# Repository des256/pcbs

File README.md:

# PCBs

Making electronics as well

## Prerequisites

KiCad 10.0
install plugin: impart GUI for KiCad
install plugin: Fabrication Toolkit
install plugin: wDark Theme
install repository: CD_FER's KiCad repository (https://raw.githubusercontent.com/CDFER/cd_fer-kicad-repository/main/repository.json)
install plugin: JLCPCB: KiCad Library

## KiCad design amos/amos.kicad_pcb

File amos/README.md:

# Amos

Jetson helper board (USB3 + 12V RS-485 Servo + 5V UART Servo)

Input Power: 19V laptop
Output Power: 19V jetson + 12V (10A..20A) servo + 5V (5A..10A) servo + 5V (5A) USB

Upstream USB Hub: USB3-C
Downstream USB Hub: 3x USB3-A + 1x internal to CH344Q

each servo bus either 12V 4-pin RS-485 or 5V 3-pin UART
selectable with DIP

## Schematic Sheets

2: Main Power + Jetson
3: Buck 12V 10A..20A
4: Buck 5V 5A..10A
5: Buck 5V USB
6: Buck 3V3 + 1V1
7: USB HUB
8: CH344Q
9: Servo A
10: Servo B
11: Servo C
12: Servo D
13: USB A
14: USB B
15: USB C

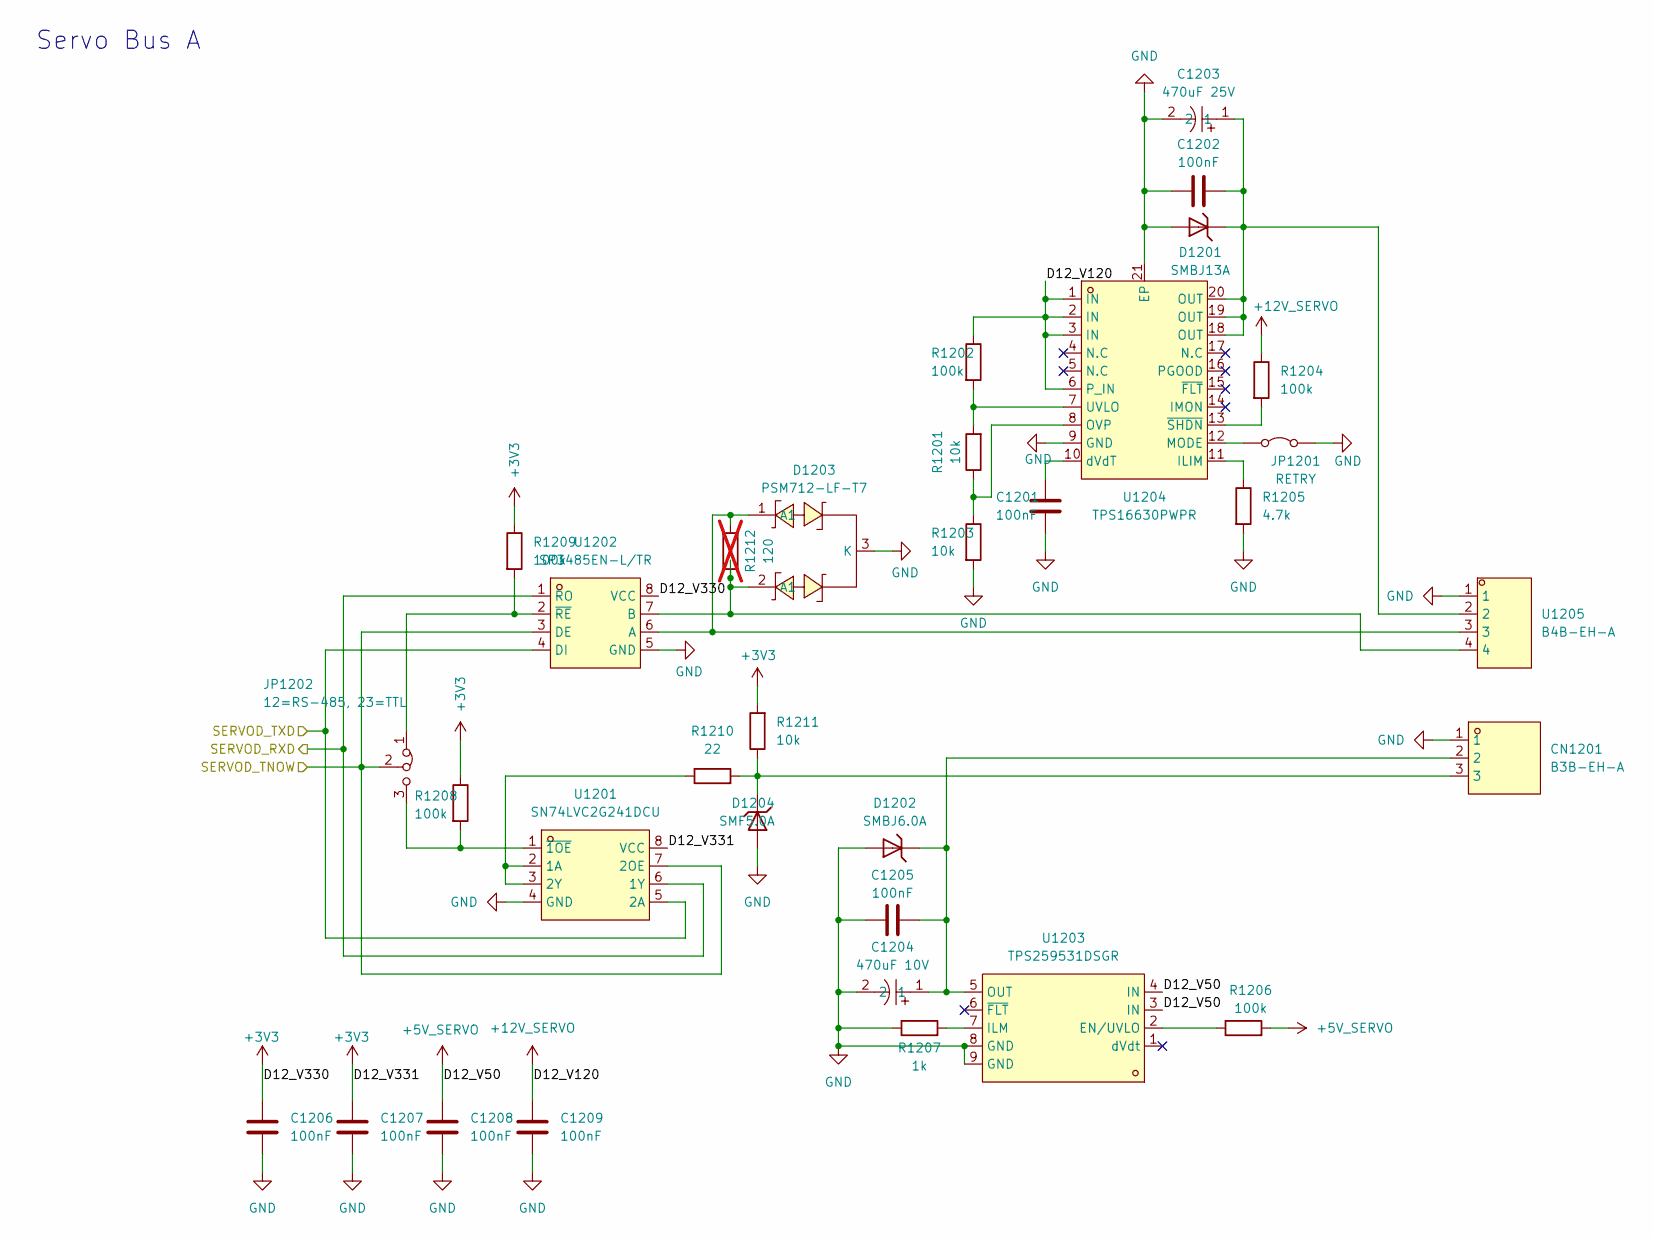
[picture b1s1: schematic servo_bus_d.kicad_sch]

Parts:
C1201, C1202, C1205: 100nF; C_0402_1005Metric; LCSC C307331
C1203: 470uF 25V; CP_Elec_8x10.5; LCSC C46550466
C1204: 470uF 10V; CP_Elec_6.3x7.7; LCSC C46550459
C1206, C1207, C1208, C1209: 100nF; C_0402_1005Metric; LCSC Part C14663
CN1201: B3B-EH-A; CONN-TH_B3B-EH-A-LF-SN; MPN B3B-EH-A(LF)(SN); LCSC Part C160259
D1201: SMBJ13A; SMB_L4.4-W3.6-LS5.3-RD; LCSC C19077567
D1202: SMBJ6.0A; SMB_L4.4-W3.6-LS5.3-RD; LCSC C19077560
D1203: PSM712-LF-T7; SOT-23-3_L3.0-W1.7-P0.95-LS2.9-BR; MPN PSM712-LF-T7; LCSC Part C32677
D1204: SMF5.0A; SOD-123FL_L2.8-W1.9-LS3.7-RD; LCSC C19077497
JP1201: RETRY; PinHeader_1x02_P2.54mm_Vertical; MPN PZ254V-11-02P; LCSC Part C492401
JP1202: 12=RS-485, 23=TTL; PinHeader_1x03_P2.54mm_Vertical; MPN PZ254V-11-03P; LCSC Part C2937625
R1201, R1203, R1211: 10k; R_0402_1005Metric; LCSC C25744
R1202, R1204, R1206, R1208, R1209: 100k; R_0402_1005Metric; LCSC C25741
R1205: 4.7k; R_0402_1005Metric; LCSC C25900
R1207: 1k; R_0402_1005Metric; LCSC C11702
R1210: 22; R_0402_1005Metric; LCSC C25092
R1212: 120; R_0603; LCSC C22787; not fitted
U1201: SN74LVC2G241DCU; VSSOP-8_L2.3-W2.0-P0.50-LS3.1-BR; MPN SN74LVC2G241DCUR; LCSC Part C10430
U1202: SP3485EN-L/TR; SOIC-8_L5.0-W4.0-P1.27-LS6.0-BL; MPN SP3485EN-L/TR; LCSC Part C8963
U1203: TPS259531DSGR; WSON-8_L2.0-W2.0-P0.50-TL-EP; MPN TPS259531DSGR; LCSC Part C2155674
U1204: TPS16630PWPR; HTSSOP-20_L6.5-W4.4-P0.65-LS6.4-TL-EP2.58; MPN TPS16630PWPR; LCSC Part C1849461
U1205: B4B-EH-A; CONN-TH_B4B-EH-A-LF-SN; MPN B4B-EH-A(LF)(SN); LCSC Part C160258

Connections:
+3V3: C1206.1, C1207.1, R1208.1, R1209.1, R1211.2, U1201.8 (VCC), U1202.8 (VCC); also elsewhere on the board
+5V_SERVO: C1208.1, R1206.2, U1203.3 (IN), U1203.4 (IN); also elsewhere on the board
+12V_SERVO: C1209.1, R1202.1, R1204.1, U1204.1 (IN), U1204.2 (IN), U1204.3 (IN), U1204.6 (P_IN); also elsewhere on the board
/SERVOD_RXD: U1201.6 (1Y), U1202.1 (RO); also elsewhere on the board
/SERVOD_TNOW: JP1202.2 (C), U1201.7 (2OE), U1202.3 (DE); also elsewhere on the board
/SERVOD_TXD: U1201.5 (2A), U1202.4 (DI); also elsewhere on the board
GND: C1201.2, C1202.1, C1203.2, C1204.2, C1205.1, C1206.2, C1207.2, C1208.2, C1209.2, CN1201.1, D1201.2, D1202.2, D1203.3 (K), D1204.2, JP1201.2 (B), R1203.2, R1205.2, R1207.1, U1201.4 (GND), U1202.5 (GND), U1203.8 (GND), U1203.9 (GND), U1204.9 (GND), U1204.21 (EP), U1205.1; also elsewhere on the board
unnamed: C1202.2, C1203.1, D1201.1, U1204.18 (OUT), U1204.19 (OUT), U1204.20 (OUT), U1205.2
unnamed: CN1201.3, D1204.1, R1210.2, R1211.1
unnamed: JP1201.1 (A), U1204.12 (MODE)
unnamed: JP1202.1 (A), R1209.2, U1202.2 (~RE)
unnamed: JP1202.3 (B), R1208.2, U1201.1 (~1OE)
unnamed: R1210.1, U1201.2 (1A), U1201.3 (2Y)
unnamed: D1203.1 (A1), R1212.1, U1202.6 (A), U1205.3
unnamed: D1203.2 (A1), R1212.2, U1202.7 (B), U1205.4
unnamed: R1206.1, U1203.2 (EN/UVLO)
unnamed: R1207.2, U1203.7 (ILM)
unnamed: C1204.1, C1205.2, CN1201.2, D1202.1, U1203.5 (OUT)
unnamed: R1205.1, U1204.11 (ILIM)
unnamed: R1201.1, R1203.1, U1204.8 (OVP)
unnamed: R1201.2, R1202.2, U1204.7 (UVLO)
unnamed: C1201.1, U1204.10 (dVdT)
unnamed: R1204.2, U1204.13 (~SHDN)

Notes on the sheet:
Servo Bus A

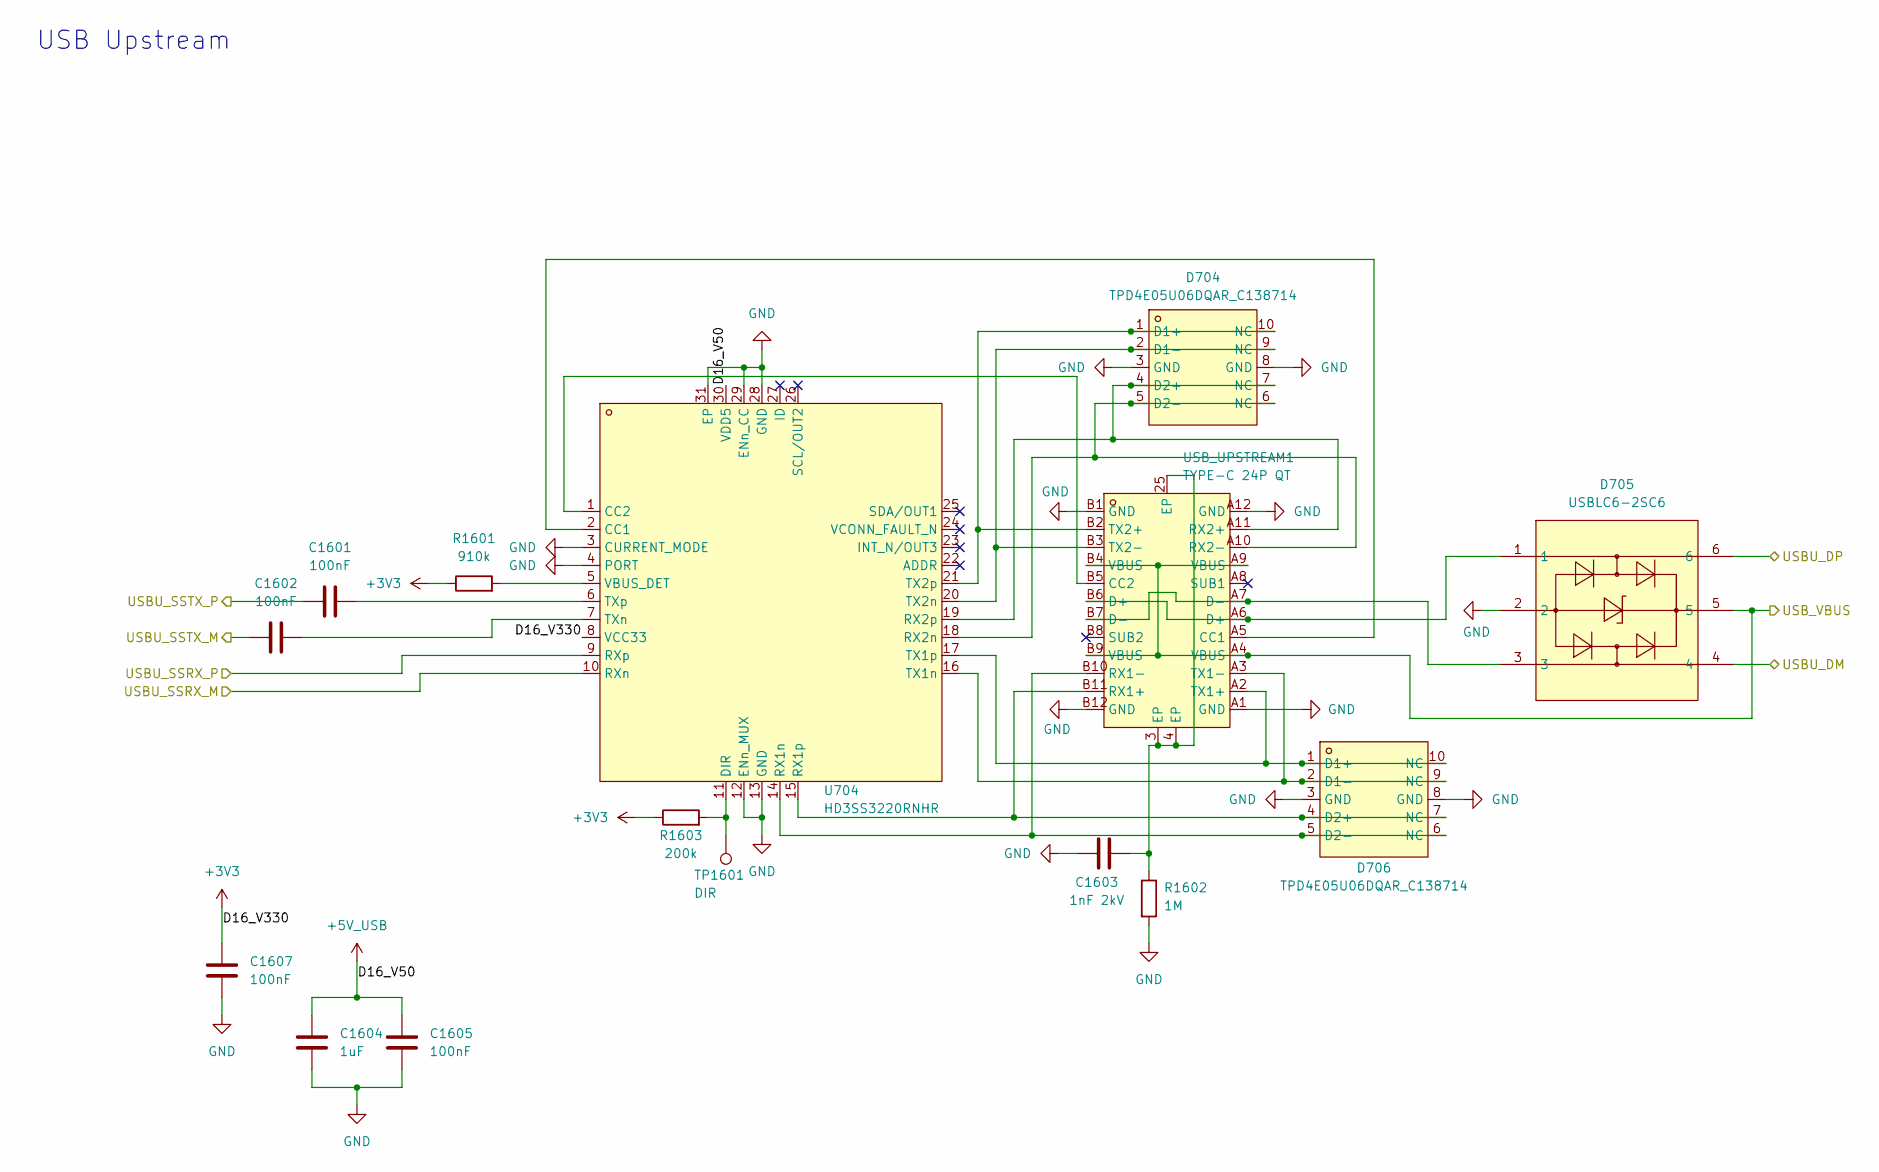
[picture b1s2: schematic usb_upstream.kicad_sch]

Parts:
C1601, C1602: 100nF; C_0402_1005Metric; LCSC C307331
C1603: 1nF 2kV; C_1206_3216Metric; LCSC C9196
C1604: 1uF; C_0402_1005Metric; LCSC Part C15849
C1605, C1607: 100nF; C_0402_1005Metric; LCSC Part C14663
D704, D706: TPD4E05U06DQAR_C138714; USON-10_L2.5-W1.0-P0.50-BL; MPN TPD4E05U06DQAR; LCSC Part C138714
D705: USBLC6-2SC6; SOT-23-6_L2.9-W1.6-P0.95-LS2.8-BL; MPN USBLC6-2SC6; LCSC Part C7519
R1601: 910k; R_0402_1005Metric; LCSC C25800
R1602: 1M; R_0402_1005Metric; LCSC C26083
R1603: 200k; R_0402_1005Metric; LCSC C25764
TP1601: DIR; TestPoint_Pad_1.0x1.0mm
U704: HD3SS3220RNHR; WQFN-30_L4.5-W2.5-P0.4-BL-EP; MPN HD3SS3220RNHR; LCSC Part C165155
USB_UPSTREAM1: TYPE-C 24P QT; USB-C-SMD_TYPE-C-24P-QT; MPN TYPE-C 24P QT; LCSC Part C2681555

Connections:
+3V3: C1607.1, R1601.1, R1603.1, U704.8 (VCC33); also elsewhere on the board
+5V_USB: C1604.1, C1605.1, U704.30 (VDD5); also elsewhere on the board
/USBU_DM: D705.4; also elsewhere on the board
/USBU_DP: D705.6; also elsewhere on the board
/USBU_SSRX_M: U704.10 (RXn); also elsewhere on the board
/USBU_SSRX_P: U704.9 (RXp); also elsewhere on the board
/USBU_SSTX_M: C1602.1; also elsewhere on the board
/USBU_SSTX_P: C1601.1; also elsewhere on the board
/USB_VBUS: D705.5, USB_UPSTREAM1.A4 (VBUS), USB_UPSTREAM1.A9 (VBUS), USB_UPSTREAM1.B4 (VBUS), USB_UPSTREAM1.B9 (VBUS); also elsewhere on the board
GND: C1603.1, C1604.2, C1605.2, C1607.2, D704.3 (GND), D704.8 (GND), D705.2, D706.3 (GND), D706.8 (GND), R1602.2, U704.3 (CURRENT_MODE), U704.4 (PORT), U704.12 (ENn_MUX), U704.13 (GND), U704.28 (GND), U704.29 (ENn_CC), U704.31 (EP), USB_UPSTREAM1.A1 (GND), USB_UPSTREAM1.A12 (GND), USB_UPSTREAM1.B1 (GND), USB_UPSTREAM1.B12 (GND); also elsewhere on the board
unnamed: C1603.2, R1602.1, USB_UPSTREAM1.3 (EP), USB_UPSTREAM1.4 (EP), USB_UPSTREAM1.25 (EP)
unnamed: D704.1 (D1+), D704.10 (NC), U704.21 (TX2p), USB_UPSTREAM1.B2 (TX2+)
unnamed: D704.2 (D1-), D704.9 (NC), U704.20 (TX2n), USB_UPSTREAM1.B3 (TX2-)
unnamed: D704.4 (D2+), D704.7 (NC), U704.19 (RX2p), USB_UPSTREAM1.A11 (RX2+)
unnamed: D704.5 (D2-), D704.6 (NC), U704.18 (RX2n), USB_UPSTREAM1.A10 (RX2-)
unnamed: D705.1, USB_UPSTREAM1.A6 (D+), USB_UPSTREAM1.B6 (D+)
unnamed: D705.3, USB_UPSTREAM1.A7 (D-), USB_UPSTREAM1.B7 (D-)
unnamed: D706.1 (D1+), D706.10 (NC), U704.17 (TX1p), USB_UPSTREAM1.A2 (TX1+)
unnamed: D706.2 (D1-), D706.9 (NC), U704.16 (TX1n), USB_UPSTREAM1.A3 (TX1-)
unnamed: D706.4 (D2+), D706.7 (NC), U704.15 (RX1p), USB_UPSTREAM1.B11 (RX1+)
unnamed: D706.5 (D2-), D706.6 (NC), U704.14 (RX1n), USB_UPSTREAM1.B10 (RX1-)
unnamed: U704.2 (CC1), USB_UPSTREAM1.A5 (CC1)
unnamed: U704.1 (CC2), USB_UPSTREAM1.B5 (CC2)
unnamed: R1603.2, TP1601.1 (1_1), U704.11 (DIR)
unnamed: C1602.2, U704.7 (TXn)
unnamed: C1601.2, U704.6 (TXp)
unnamed: R1601.2, U704.5 (VBUS_DET)

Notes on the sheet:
USB Upstream

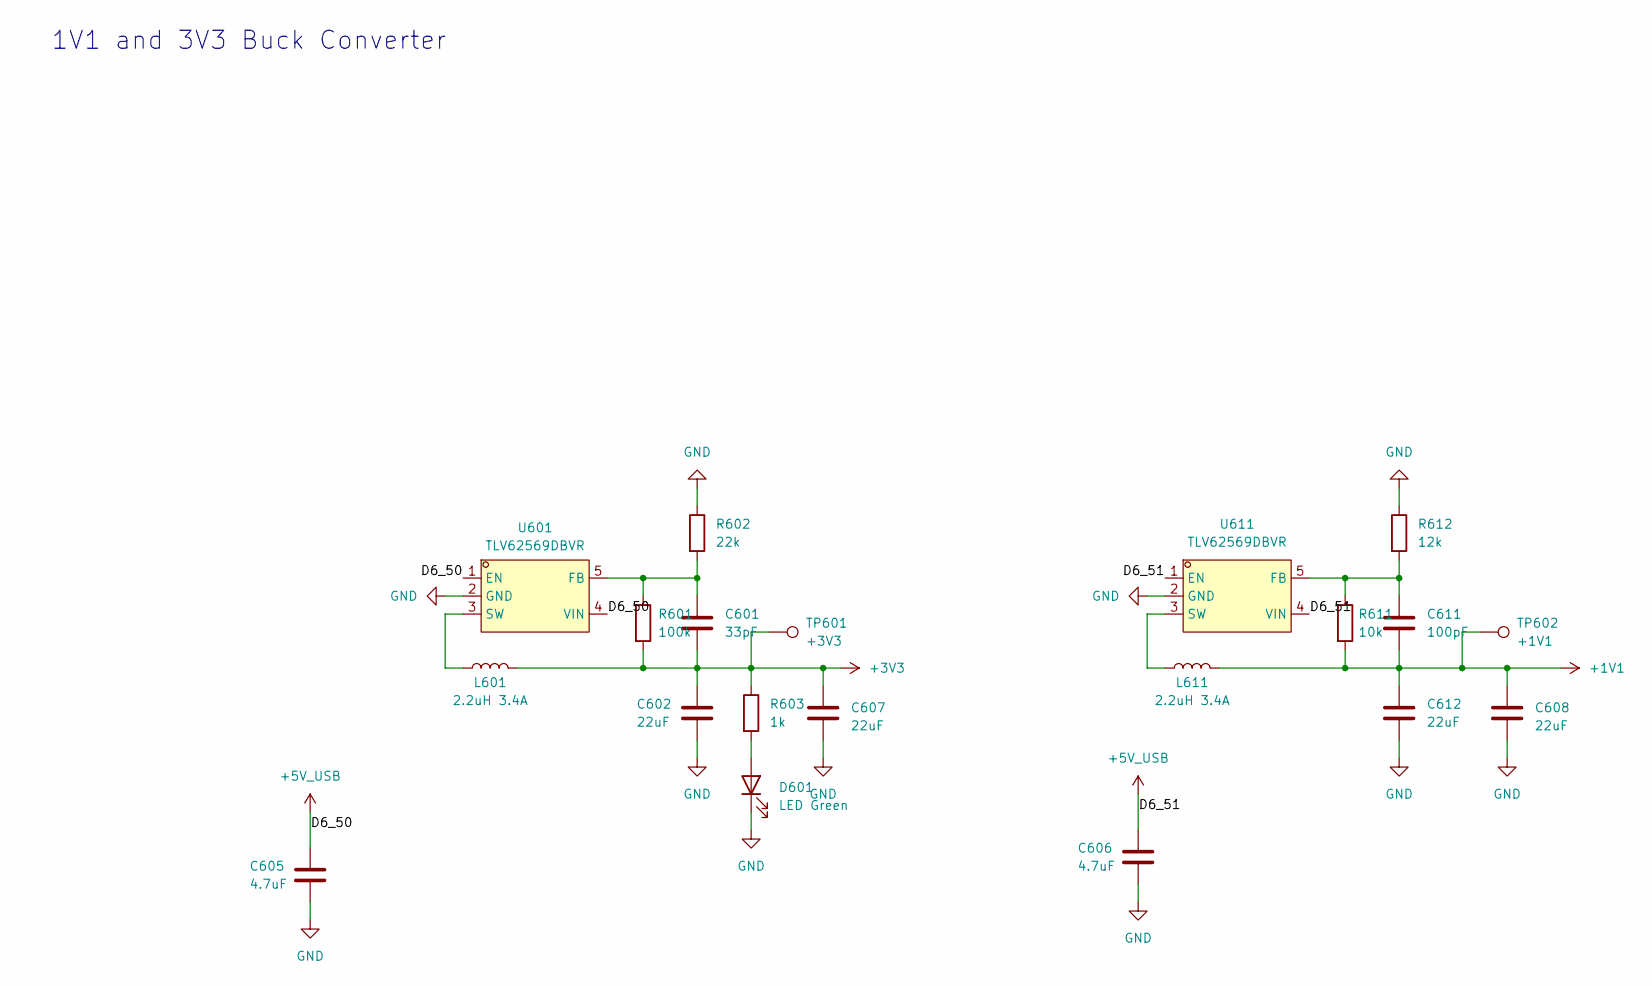
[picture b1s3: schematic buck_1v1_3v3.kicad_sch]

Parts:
C601: 33pF; C_0402_1005Metric; LCSC Part C1562
C602, C607, C608, C612: 22uF; C_0805_2012Metric; LCSC Part C45783
C605, C606: 4.7uF; C_0805_2012Metric; LCSC Part C1779
C611: 100pF; C_0402_1005Metric; LCSC Part C1546
D601: LED Green; LED_0805_2012Metric; LCSC C2297
L601, L611: 2.2uH 3.4A; IND-SMD_L4.0-W4.0_LQH44PN2R2MP0L; MPN SMNR4020-2.2UH; LCSC Part C135262
R601: 100k; R_0402_1005Metric; LCSC C25741
R602: 22k; R_0402_1005Metric; LCSC C25768
R603: 1k; R_0402_1005Metric; LCSC C11702
R611: 10k; R_0402_1005Metric; LCSC C25744
R612: 12k; R_0402_1005Metric; LCSC C25752
TP601: +3V3; TestPoint_Pad_1.0x1.0mm
TP602: +1V1; TestPoint_Pad_1.0x1.0mm
U601, U611: TLV62569DBVR; SOT-23-5_L3.0-W1.7-P0.95-LS2.8-BR; MPN TLV62569DBVR; LCSC Part C141836

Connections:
+1V1: C608.1, C611.2, C612.1, L611.2, R611.2, TP602.1 (1_1); also elsewhere on the board
+3V3: C601.2, C602.1, C607.1, L601.2, R601.2, R603.1, TP601.1 (1_1); also elsewhere on the board
+5V_USB: C605.1, C606.1, U601.1 (EN), U601.4 (VIN), U611.1 (EN), U611.4 (VIN); also elsewhere on the board
GND: C602.2, C605.2, C606.2, C607.2, C608.2, C612.2, D601.1 (K), R602.1, R612.1, U601.2 (GND), U611.2 (GND); also elsewhere on the board
unnamed: D601.2 (A), R603.2
unnamed: C601.1, R601.1, R602.2, U601.5 (FB)
unnamed: L601.1, U601.3 (SW)
unnamed: C611.1, R611.1, R612.2, U611.5 (FB)
unnamed: L611.1, U611.3 (SW)

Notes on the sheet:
1V1 and 3V3 Buck Converter

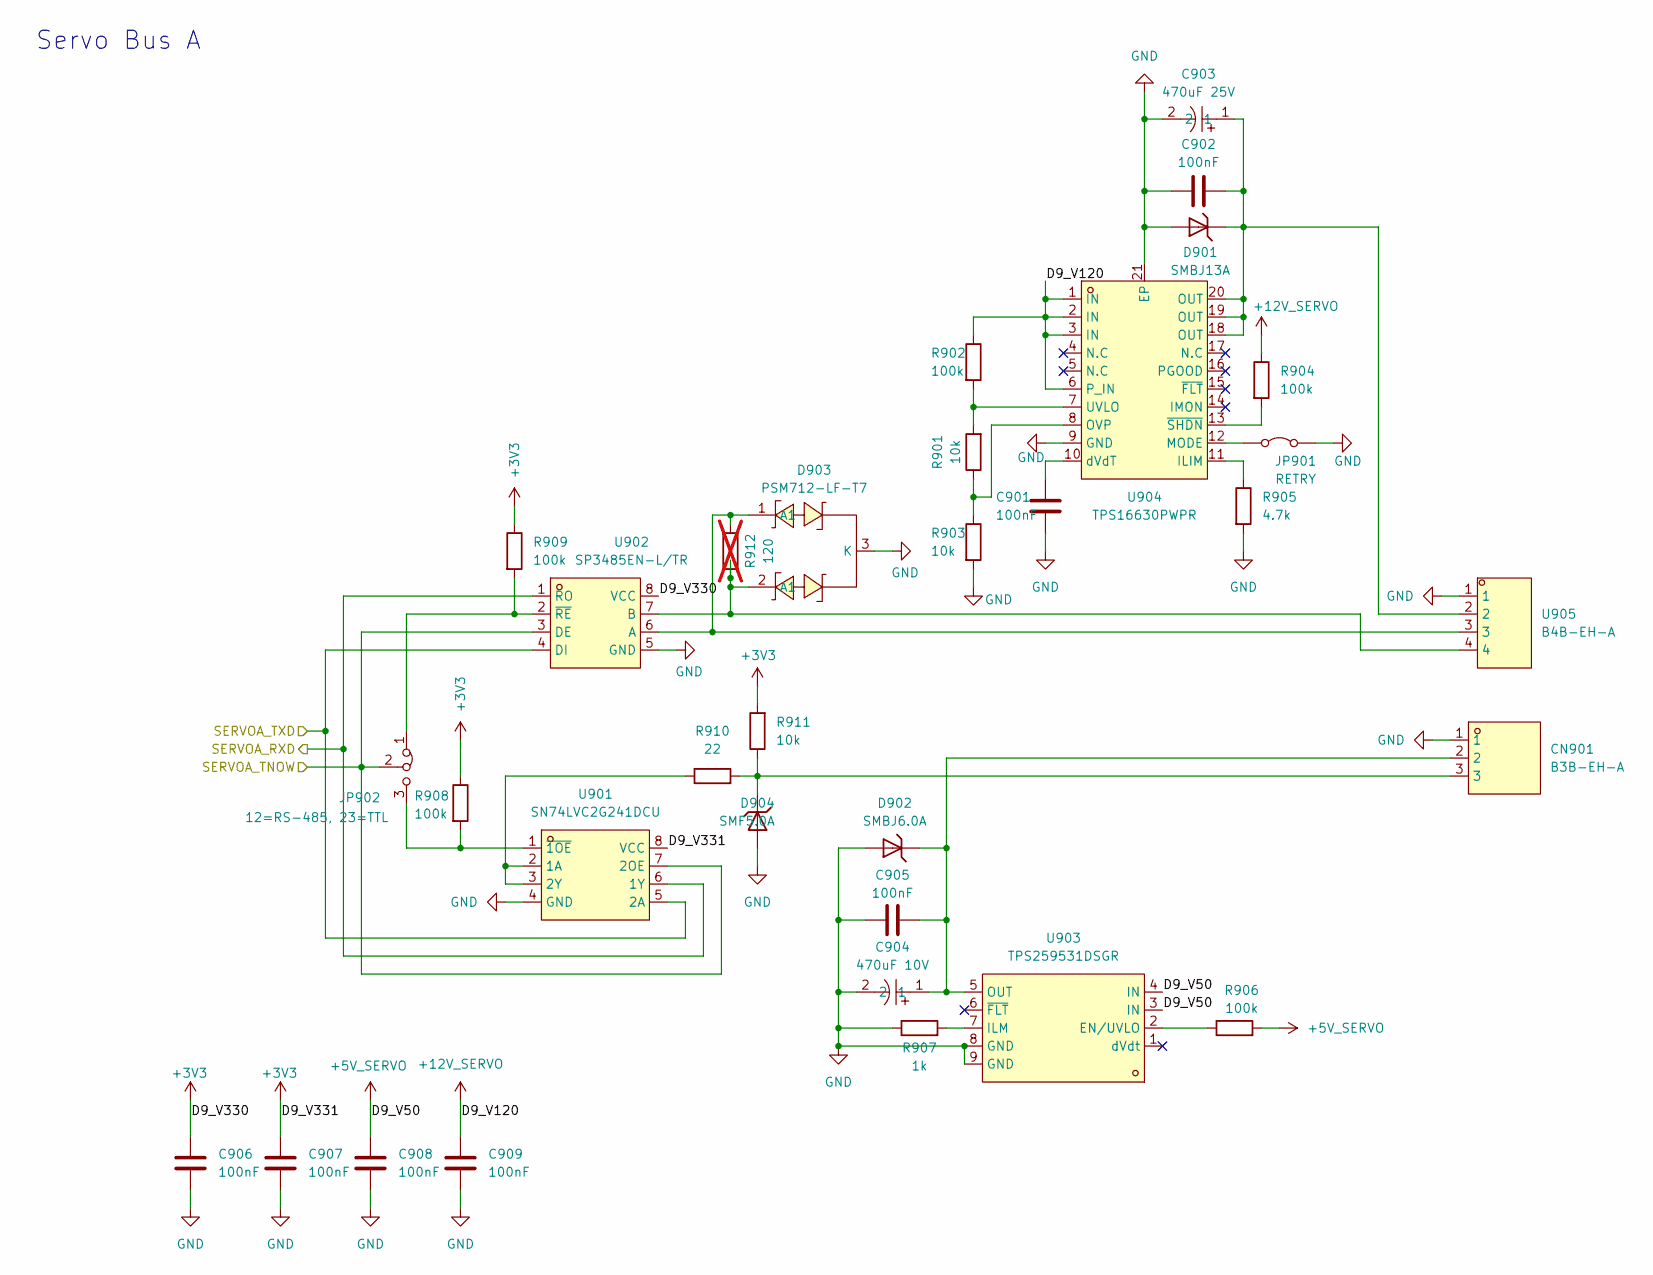
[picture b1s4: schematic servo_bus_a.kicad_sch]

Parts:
C901, C902, C905: 100nF; C_0402_1005Metric; LCSC C307331
C903: 470uF 25V; CP_Elec_8x10.5; LCSC C46550466
C904: 470uF 10V; CP_Elec_6.3x7.7; LCSC C46550459
C906, C907, C908, C909: 100nF; C_0402_1005Metric; LCSC Part C14663
CN901: B3B-EH-A; CONN-TH_B3B-EH-A-LF-SN; MPN B3B-EH-A(LF)(SN); LCSC Part C160259
D901: SMBJ13A; SMB_L4.4-W3.6-LS5.3-RD; LCSC C19077567
D902: SMBJ6.0A; SMB_L4.4-W3.6-LS5.3-RD; LCSC C19077560
D903: PSM712-LF-T7; SOT-23-3_L3.0-W1.7-P0.95-LS2.9-BR; MPN PSM712-LF-T7; LCSC Part C32677
D904: SMF5.0A; SOD-123FL_L2.8-W1.9-LS3.7-RD; LCSC C19077497
JP901: RETRY; PinHeader_1x02_P2.54mm_Vertical; MPN PZ254V-11-02P; LCSC Part C492401
JP902: 12=RS-485, 23=TTL; PinHeader_1x03_P2.54mm_Vertical; MPN PZ254V-11-03P; LCSC Part C2937625
R901, R903, R911: 10k; R_0402_1005Metric; LCSC C25744
R902, R904, R906, R908, R909: 100k; R_0402_1005Metric; LCSC C25741
R905: 4.7k; R_0402_1005Metric; LCSC C25900
R907: 1k; R_0402_1005Metric; LCSC C11702
R910: 22; R_0402_1005Metric; LCSC C25092
R912: 120; R_0603; LCSC C22787; not fitted
U901: SN74LVC2G241DCU; VSSOP-8_L2.3-W2.0-P0.50-LS3.1-BR; MPN SN74LVC2G241DCUR; LCSC Part C10430
U902: SP3485EN-L/TR; SOIC-8_L5.0-W4.0-P1.27-LS6.0-BL; MPN SP3485EN-L/TR; LCSC Part C8963
U903: TPS259531DSGR; WSON-8_L2.0-W2.0-P0.50-TL-EP; MPN TPS259531DSGR; LCSC Part C2155674
U904: TPS16630PWPR; HTSSOP-20_L6.5-W4.4-P0.65-LS6.4-TL-EP2.58; MPN TPS16630PWPR; LCSC Part C1849461
U905: B4B-EH-A; CONN-TH_B4B-EH-A-LF-SN; MPN B4B-EH-A(LF)(SN); LCSC Part C160258

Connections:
+3V3: C906.1, C907.1, R908.1, R909.1, R911.2, U901.8 (VCC), U902.8 (VCC); also elsewhere on the board
+5V_SERVO: C908.1, R906.2, U903.3 (IN), U903.4 (IN); also elsewhere on the board
+12V_SERVO: C909.1, R902.1, R904.1, U904.1 (IN), U904.2 (IN), U904.3 (IN), U904.6 (P_IN); also elsewhere on the board
/SERVOA_RXD: U901.6 (1Y), U902.1 (RO); also elsewhere on the board
/SERVOA_TNOW: JP902.2 (C), U901.7 (2OE), U902.3 (DE); also elsewhere on the board
/SERVOA_TXD: U901.5 (2A), U902.4 (DI); also elsewhere on the board
GND: C901.2, C902.1, C903.2, C904.2, C905.1, C906.2, C907.2, C908.2, C909.2, CN901.1, D901.2, D902.2, D903.3 (K), D904.2, JP901.2 (B), R903.2, R905.2, R907.1, U901.4 (GND), U902.5 (GND), U903.8 (GND), U903.9 (GND), U904.9 (GND), U904.21 (EP), U905.1; also elsewhere on the board
unnamed: C902.2, C903.1, D901.1, U904.18 (OUT), U904.19 (OUT), U904.20 (OUT), U905.2
unnamed: CN901.3, D904.1, R910.2, R911.1
unnamed: JP901.1 (A), U904.12 (MODE)
unnamed: JP902.1 (A), R909.2, U902.2 (~RE)
unnamed: JP902.3 (B), R908.2, U901.1 (~1OE)
unnamed: R910.1, U901.2 (1A), U901.3 (2Y)
unnamed: D903.1 (A1), R912.1, U902.6 (A), U905.3
unnamed: D903.2 (A1), R912.2, U902.7 (B), U905.4
unnamed: R906.1, U903.2 (EN/UVLO)
unnamed: R907.2, U903.7 (ILM)
unnamed: C904.1, C905.2, CN901.2, D902.1, U903.5 (OUT)
unnamed: R905.1, U904.11 (ILIM)
unnamed: R901.1, R903.1, U904.8 (OVP)
unnamed: R901.2, R902.2, U904.7 (UVLO)
unnamed: C901.1, U904.10 (dVdT)
unnamed: R904.2, U904.13 (~SHDN)

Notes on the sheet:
Servo Bus A

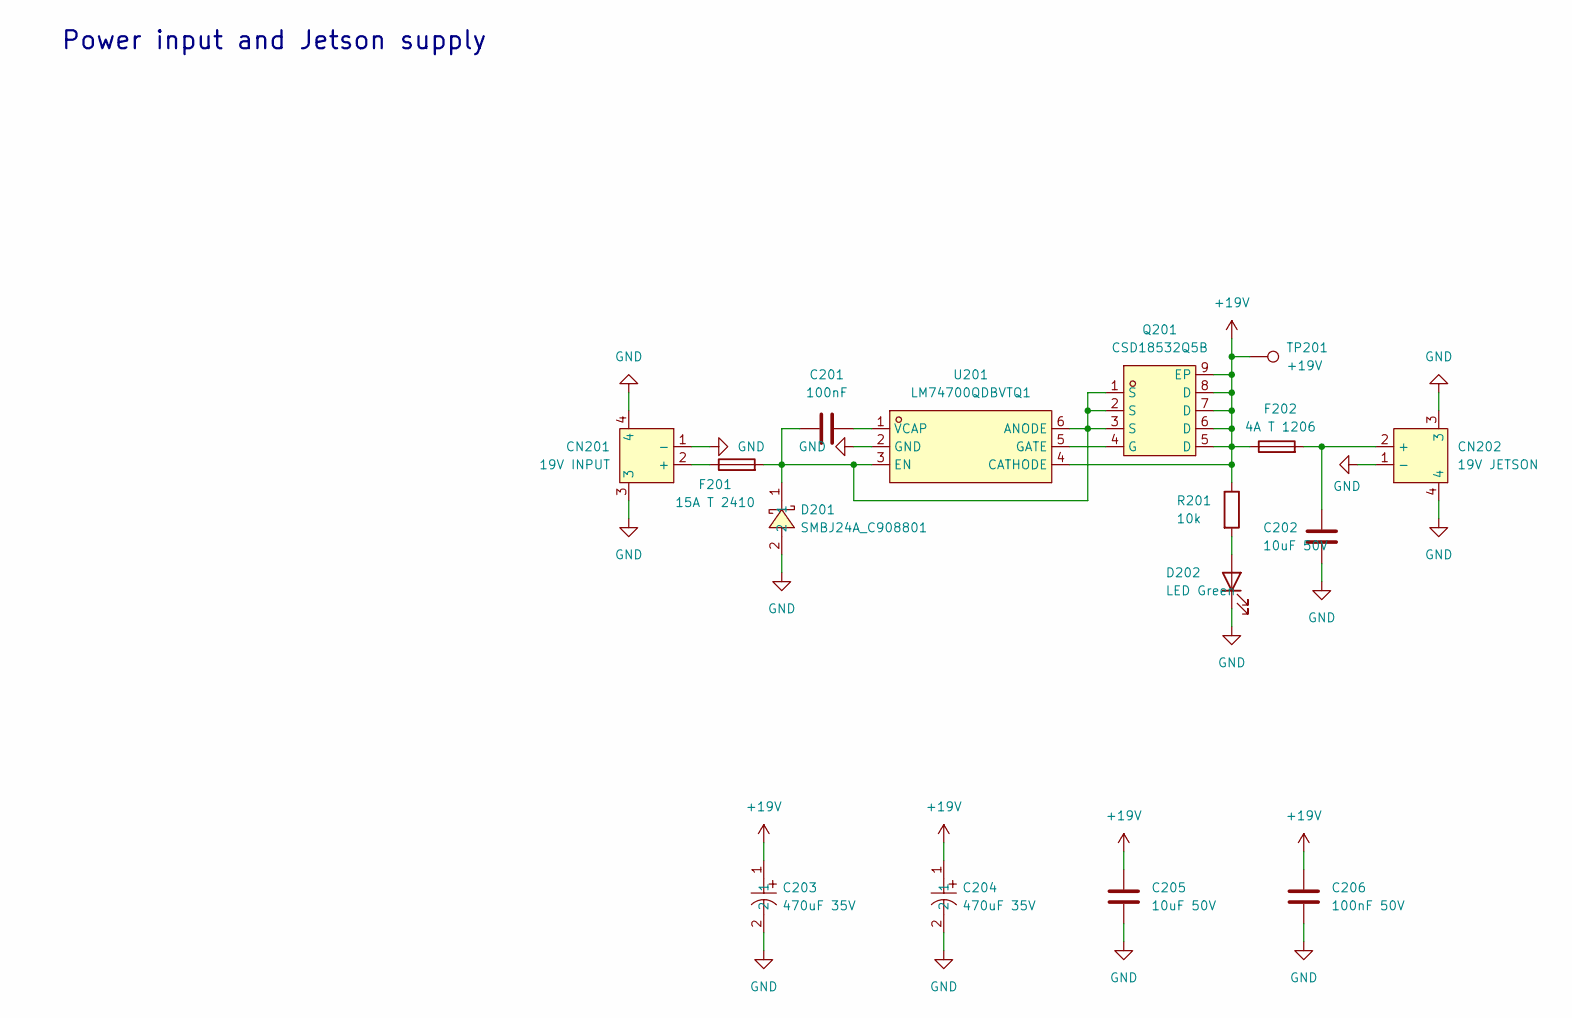
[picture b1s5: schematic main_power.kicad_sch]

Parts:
C201: 100nF; C_0402_1005Metric; LCSC C307331
C202, C205: 10uF 50V; C_1206_3216Metric; LCSC C13585
C203, C204: 470uF 35V; CAP-SMD_BD10.0-L10.3-W10.3-LS11.3-FD; MPN RVE470UF35V167RV084; LCSC Part C5155332
C206: 100nF 50V; C_0603_1608Metric; LCSC C14663
CN201: 19V INPUT; CONN-TH_XT30PW-M; MPN XT30PW-M30.G.Y; LCSC Part C431092
CN202: 19V JETSON; CONN-TH_XT30PW-M; MPN XT30PW-M30.G.Y; LCSC Part C431092
D201: SMBJ24A_C908801; SMB_L4.4-W3.6-LS5.3-RD; MPN SMBJ24A; LCSC Part C908801
D202: LED Green; LED_0805_2012Metric; LCSC C2297
F201: 15A T 2410; Fuse_2410_6125Metric; LCSC C187551
F202: 4A T 1206; Fuse_1206_3216Metric; LCSC C3157092
Q201: CSD18532Q5B; SON-8_L5.0-W6.0-P1.27-BL-1; MPN CSD18532Q5B; LCSC Part C882766
R201: 10k; R_0402_1005Metric; LCSC C25744
TP201: +19V; TestPoint_Pad_1.0x1.0mm
U201: LM74700QDBVTQ1; SOT-23-6_L2.9-W1.6-P0.95-LS2.8-TL; MPN LM74700QDBVTQ1; LCSC Part C2653623

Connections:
+19V: C203.1, C204.1, C205.1, C206.1, F202.1, Q201.5 (D), Q201.6 (D), Q201.7 (D), Q201.8 (D), Q201.9 (EP), R201.1, TP201.1 (1_1), U201.4 (CATHODE); also elsewhere on the board
GND: C202.2, C203.2, C204.2, C205.2, C206.2, CN201.1 (-), CN201.3, CN201.4, CN202.1 (-), CN202.3, CN202.4, D201.2, D202.1 (K), U201.2 (GND); also elsewhere on the board
unnamed: CN201.2 (+), F201.1
unnamed: C202.1, CN202.2 (+), F202.2
unnamed: D202.2 (A), R201.2
unnamed: Q201.4 (G), U201.5 (GATE)
unnamed: C201.1, D201.1, F201.2, Q201.1 (S), Q201.2 (S), Q201.3 (S), U201.3 (EN), U201.6 (ANODE)
unnamed: C201.2, U201.1 (VCAP)

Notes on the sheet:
Power input and Jetson supply

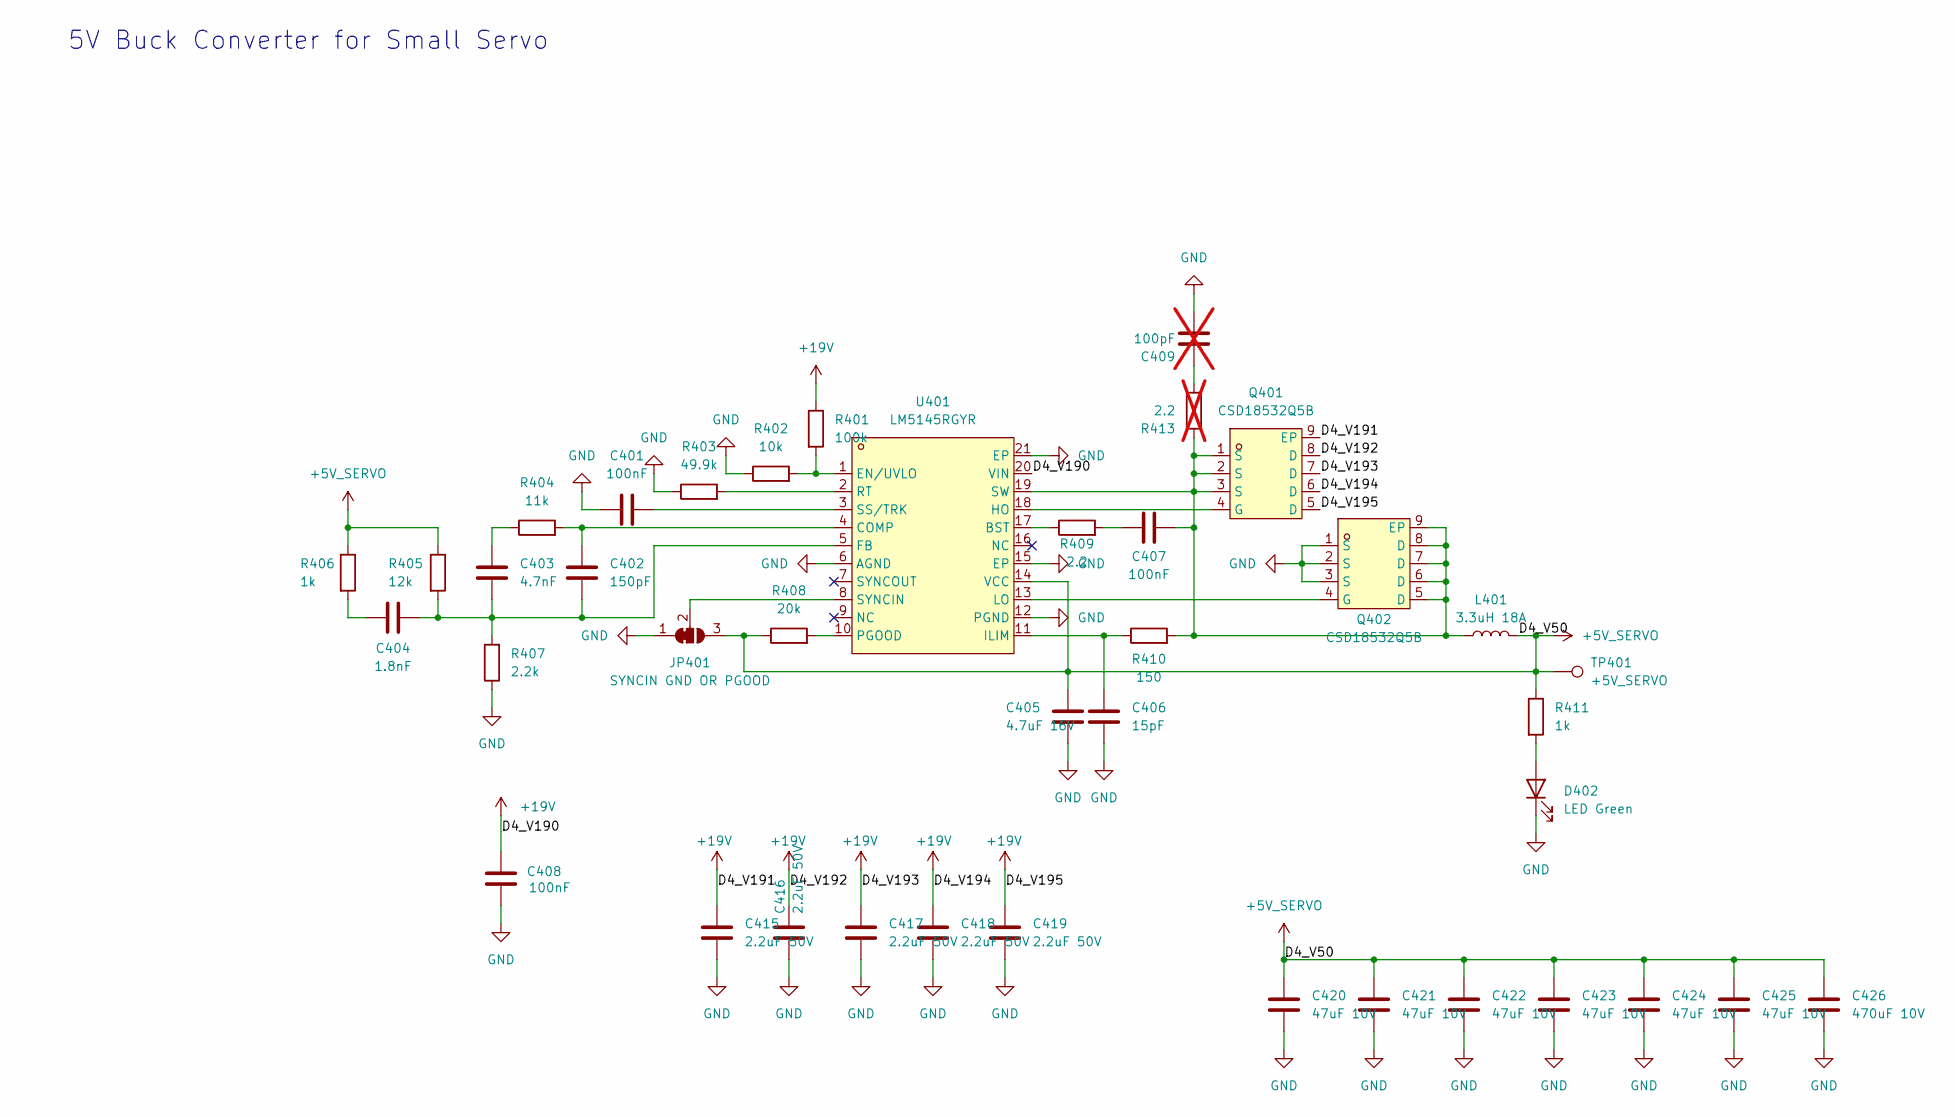
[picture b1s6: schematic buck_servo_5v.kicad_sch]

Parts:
C401, C407, C408: 100nF; C_0402_1005Metric; LCSC C307331
C402: 150pF; C_0402_1005Metric; LCSC C1527
C403: 4.7nF; C_0402_1005Metric; LCSC C1538
C404: 1.8nF; C_0402_1005Metric; LCSC C107024
C405: 4.7uF 16V; C_0603_1608Metric; LCSC C19666
C406: 15pF; C_0402_1005Metric; LCSC C1548
C409: 100pF; C_0603_1608Metric; LCSC C14858; not fitted
C415, C416, C417, C418, C419: 2.2uF 50V; C_1206_3216Metric; LCSC Part C50254
C420, C421, C422, C423, C424, C425: 47uF 10V; C_1206_3216Metric; LCSC Part C96123
C426: 470uF 10V; CAP-SMD_BD6.3-L6.6-W6.6-LS7.3-FD-H7.7; LCSC Part C46550459
D402: LED Green; LED_0805_2012Metric; LCSC C2297
JP401: SYNCIN GND OR PGOOD; SolderJumper-3_P1.3mm_Bridged12_Pad1.0x1.5mm
L401: 3.3uH 18A; L_Vishay_IHLP-4040; MPN IHLP4040DZER3R3M01; LCSC Part C845075
Q401, Q402: CSD18532Q5B; SON-8_L5.0-W6.0-P1.27-BL-1; MPN CSD18532Q5B; LCSC Part C882766
R401: 100k; R_0402_1005Metric; LCSC C25741
R402: 10k; R_0402_1005Metric; LCSC C25744
R403: 49.9k; R_0402_1005Metric; LCSC C25897
R404: 11k; R_0402_1005Metric; LCSC C25749
R405: 12k; R_0402_1005Metric; LCSC C25752
R406, R411: 1k; R_0402_1005Metric; LCSC C11702
R407: 2.2k; R_0402_1005Metric; LCSC C25879
R408: 20k; R_0402_1005Metric; LCSC C25765
R409: 2.2; R_0402_1005Metric; LCSC C25101
R410: 150; R_0402_1005Metric; LCSC C25082
R413: 2.2; R_0603; LCSC C22939; not fitted
TP401: +5V_SERVO; TestPoint_Pad_1.0x1.0mm
U401: LM5145RGYR; VQFN-20_L4.5-W3.5-P0.50-BL-EP; MPN LM5145RGYR; LCSC Part C485912

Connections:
+5V_SERVO: C405.1, C420.1, C421.1, C422.1, C423.1, C424.1, C425.1, C426.1, JP401.3 (B), L401.2, R405.1, R406.1, R408.1, R411.1, TP401.1 (1_1), U401.14 (VCC); also elsewhere on the board
+19V: C408.2, C415.1, C416.1, C417.1, C418.1, C419.1, Q401.5 (D), Q401.6 (D), Q401.7 (D), Q401.8 (D), Q401.9 (EP), R401.1, U401.20 (VIN); also elsewhere on the board
GND: C401.1, C405.2, C406.2, C408.1, C409.2, C415.2, C416.2, C417.2, C418.2, C419.2, C420.2, C421.2, C422.2, C423.2, C424.2, C425.2, C426.2, D402.1 (K), JP401.1 (A), Q402.1 (S), Q402.2 (S), Q402.3 (S), R402.1, R403.1, R407.1, U401.6 (AGND), U401.12 (PGND), U401.15 (EP), U401.21 (EP); also elsewhere on the board
unnamed: C403.1, R404.1
unnamed: C404.2, R406.2
unnamed: C407.1, R409.2
unnamed: C409.1, R413.2
unnamed: D402.2 (A), R411.2
unnamed: JP401.2 (C), U401.8 (SYNCIN)
unnamed: Q401.4 (G), U401.18 (HO)
unnamed: C407.2, L401.1, Q401.1 (S), Q401.2 (S), Q401.3 (S), Q402.5 (D), Q402.6 (D), Q402.7 (D), Q402.8 (D), Q402.9 (EP), R410.2, R413.1, U401.19 (SW)
unnamed: Q402.4 (G), U401.13 (LO)
unnamed: R409.1, U401.17 (BST)
unnamed: C402.1, R404.2, U401.4 (COMP)
unnamed: R401.2, R402.2, U401.1 (EN/UVLO)
unnamed: C402.2, C403.2, C404.1, R405.2, R407.2, U401.5 (FB)
unnamed: C406.1, R410.1, U401.11 (ILIM)
unnamed: R408.2, U401.10 (PGOOD)
unnamed: R403.2, U401.2 (RT)
unnamed: C401.2, U401.3 (SS/TRK)

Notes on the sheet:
5V Buck Converter for Small Servo
